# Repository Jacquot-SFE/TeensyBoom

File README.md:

TEENSYBOOM
---
Teensy 3.2 analog emulation drum machine.

# Organization

Supposedly all of the design artifacts will wind up in here.

If it's not here, go check the ol' [synth-drum]() repo.  It's a mess, be warned.

* **/chassis/** files for the cheek blocks & control panel
* **/TeensyBoomVoiceLibrary/** source files for the Teensy-audio-based library
* **/TeensyBoom/** the sketch files for the sequencer and stuff
* **/demo-patterns/** Some pattern files captured after playing with the sequencer a bit.  For use when you get sick of the default pattern.
* **/Documentation/** ha ha.  

## Setup & Configuration

Developed using Arduino IDE 1.6.5.  Last time I tried a newer built, it rebuilt everything everytime I clicked 'go.'

Loading using Teensy Loader 1.28.

### Installation:

Copy the _TeensyVoiceLibrary_ files to your local Arduino library directory (for me , it's C:\Users\redacted\Documents\Arduino\libraries\TeensyBoomVoiceLibrary).

Remove or rename the AudioSynthSimpleDrum in the teensy audio directory (C:\Users\byron.jacquot\Documents\Arduino\libraries\Audio\synth_simple_drum.cpp and .h).  The Boom library contains a newer version.

### Compile and Load:

I've been building for 72 MHz, non-optimized, with the assumption that we can always bump up to optimization & overclocking if we run out of resources.  It's harder to go the other way!

License Information
-------------------

This product is _**open source**_!

Please review the LICENSE.md file for license information.

Distributed as-is; no warranty is given.

It heavily leverages all of the infrastructure developed by [PJRC.com](PJRC.com).  Please support them by purchasing genuine Teensy components!  _Alibaba Teensys aren't Teensies!_

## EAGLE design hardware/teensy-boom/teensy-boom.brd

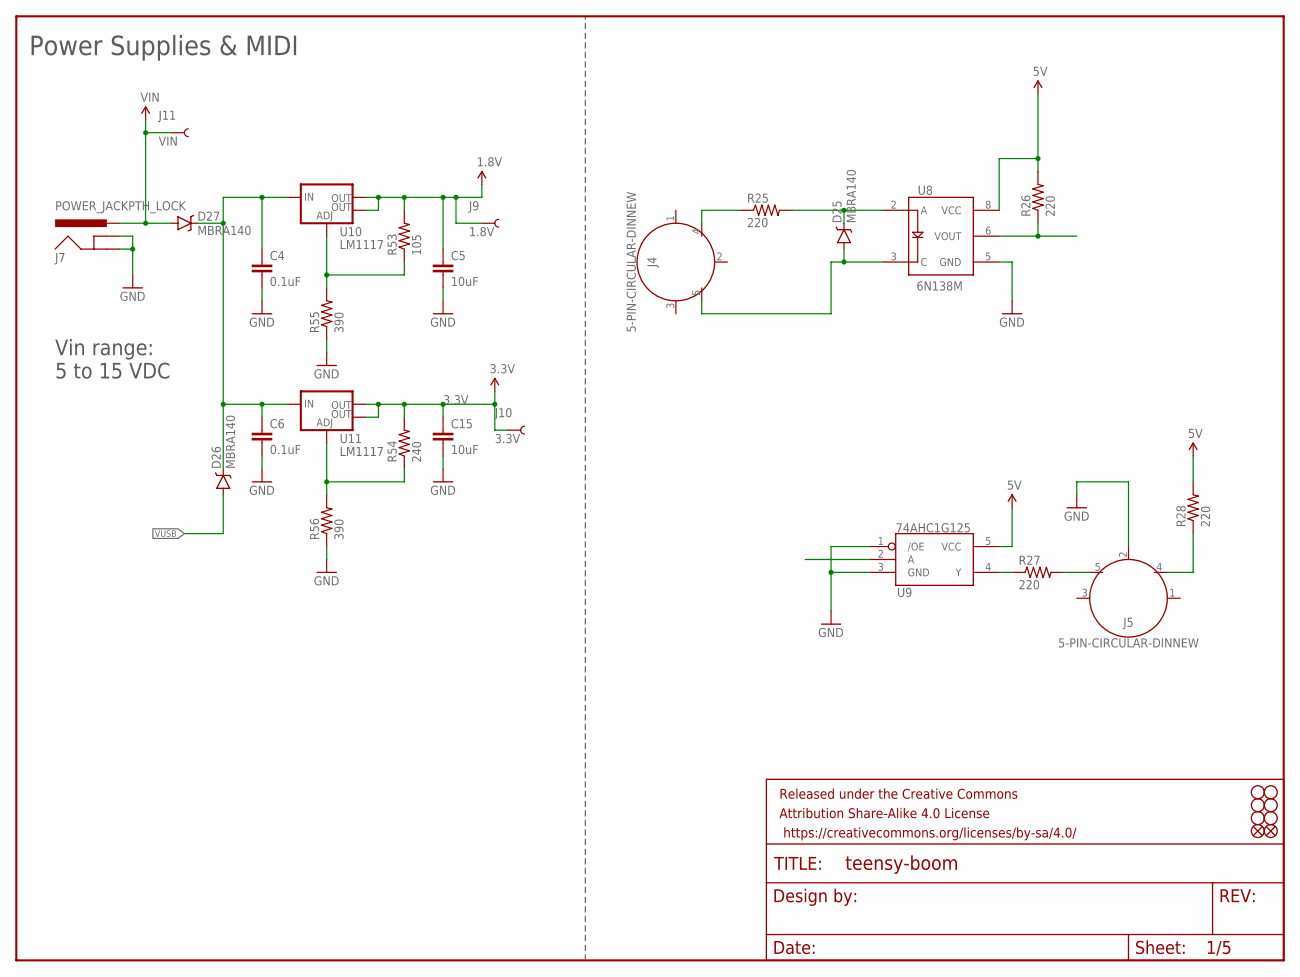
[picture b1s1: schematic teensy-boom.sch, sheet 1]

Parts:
C4, C6: 0.1uF; 0603-CAP
C5, C15: 10uF; 0603-CAP
D25, D26, D27: MBRA140; SMA-DIODE
FD1, FD2: FIDUCIALUFIDUCIAL; MICRO-FIDUCIAL
FRAME2: FRAME-LETTERNO_PACKAGE; DUMMY
H1, H2, H3, H4, H5, H6: STAND-OFF
J4, J5: 5-PIN-CIRCULAR-DINNEW; 5-PIN-DIN-RA-PCB-NEW
J7: POWER_JACKPTH_LOCK; POWER_JACK_PTH_LOCK
J9: 1.8V; TP_15TH
J10: 3.3V; TP_15TH
J11: VIN; TP_15TH
R25, R26, R27, R28: 220; 0603-RES
R53: 105; 0603-RES
R54: 240; 0603-RES
R55, R56: 390; 0603-RES
U8: 6N138M; 8-SMD
U9: 74AHC1G125; SOT23-5
U10, U11: LM1117; SOT223

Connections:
1.8V: C5.1, J9.P$1, R53.2, U10.2 (OUT), U10.4 (OUT); also elsewhere on the board
3.3V: C15.1, J10.P$1, R54.2, U11.2 (OUT), U11.4 (OUT); also elsewhere on the board
5V: R26.2, R28.2, U8.8 (VCC), U9.5 (VCC)
GND: C4.2, C5.2, C6.2, C15.2, J5.2, J7.GND, J7.GNDBREAK, R55.1, R56.1, U8.5 (GND), U9.1 (/OE), U9.3 (GND); also elsewhere on the board
unnamed: J4.4, R25.1
unnamed: D25.C, R25.2, U8.2 (A)
unnamed: D25.A, J4.5, U8.3 (C)
unnamed: R26.1, U8.6 (VOUT)
unnamed: R27.1, U9.4 (Y)
unnamed: J5.5, R27.2
unnamed: J5.4, R28.1
unnamed: C4.1, C6.1, D26.C, D27.C, U10.3 (IN), U11.3 (IN)
unnamed: R53.1, R55.2, U10.1 (ADJ)
unnamed: R54.1, R56.2, U11.1 (ADJ)
VIN: D27.A, J7.PWR, J11.P$1
VUSB: D26.A; also elsewhere on the board

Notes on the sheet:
Power Supplies & MIDI
Vin range: 5 to 15 VDC

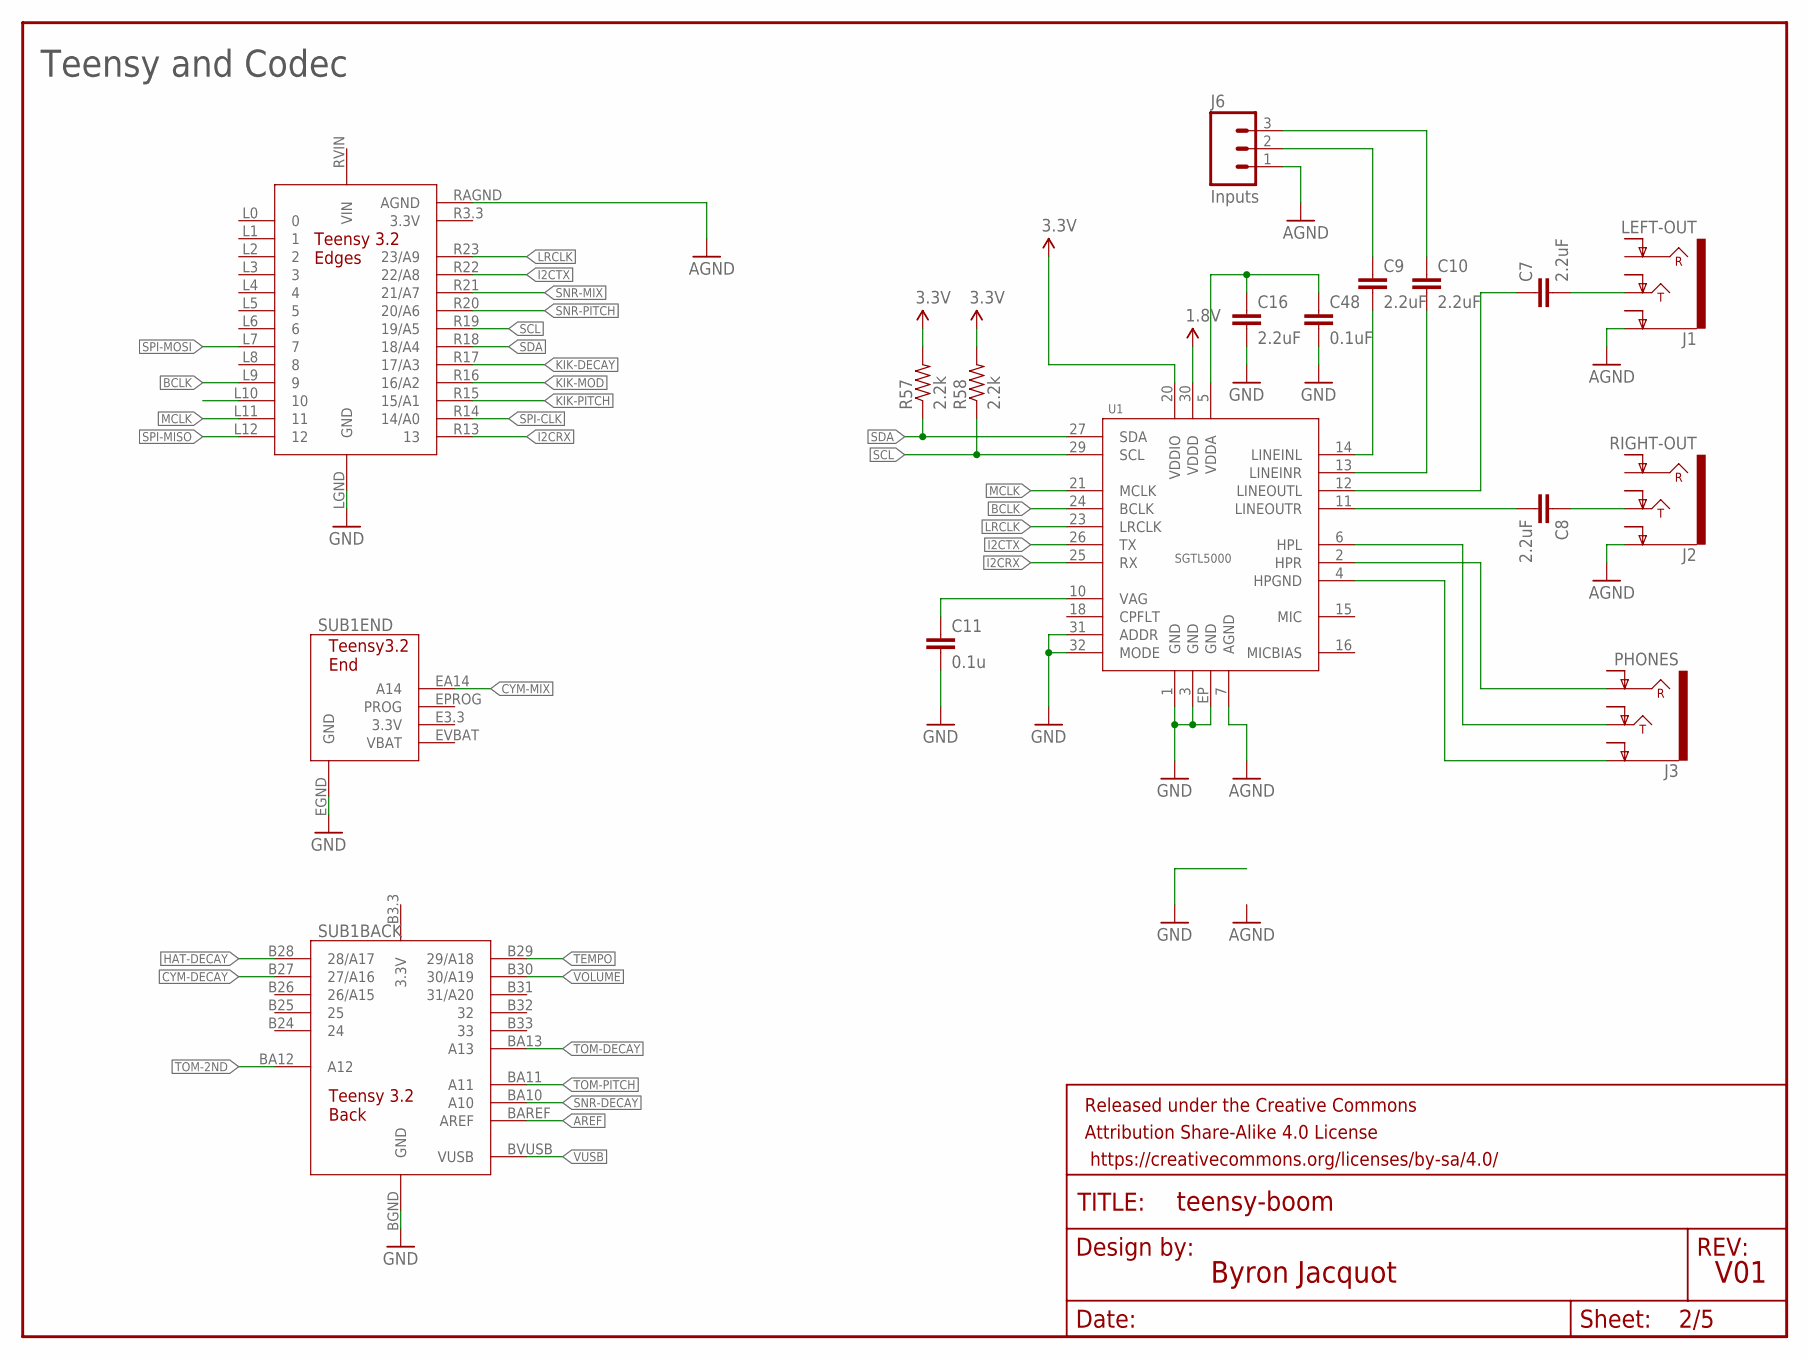
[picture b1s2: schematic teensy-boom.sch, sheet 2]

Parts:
C7, C8, C9, C10, C16: 2.2uF; 0805-CAP
C11: 0.1u; 0805
C48: 0.1uF; 0603-CAP
FRAME1: FRAME-LETTER; CREATIVE_COMMONS
J1: LEFT-OUT; AUDIO-JACK-.25-INCH-HORIZ-PTH
J2: RIGHT-OUT; AUDIO-JACK-.25-INCH-HORIZ-PTH
J3: PHONES; AUDIO-JACK-.25-INCH-HORIZ-PTH
J6: Inputs; 1X03_LOCK
R57, R58: 2.2k; 0603-RES
SUB1: TEENSY-3.2PTH; TEENSY-3.2
U1: SGTL5000; QFN-32

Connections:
1.8V: U1.30 (VDDD); also elsewhere on the board
3.3V: R57.2, R58.2, U1.20 (VDDIO); also elsewhere on the board
AGND: J1.SLEEVE (EARTH), J2.SLEEVE (EARTH), J6.1, SUB1.RAGND (AGND), U1.7 (AGND); also elsewhere on the board
AREF: SUB1.BAREF (AREF); also elsewhere on the board
BCLK: SUB1.L9 (9), U1.24 (BCLK)
CYM-DECAY: SUB1.B27 (27/A16); also elsewhere on the board
CYM-MIX: SUB1.EA14 (A14); also elsewhere on the board
GND: C11.2, C16.2, C48.2, SUB1.BGND (GND), SUB1.EGND (GND), SUB1.LGND (GND), U1.1 (GND), U1.3 (GND), U1.31 (ADDR), U1.32 (MODE), U1.EP (GND); also elsewhere on the board
HAT-DECAY: SUB1.B28 (28/A17); also elsewhere on the board
I2CRX: SUB1.R13 (13), U1.25 (RX)
I2CTX: SUB1.R22 (22/A8), U1.26 (TX)
KIK-DECAY: SUB1.R17 (17/A3); also elsewhere on the board
KIK-MOD: SUB1.R16 (16/A2); also elsewhere on the board
KIK-PITCH: SUB1.R15 (15/A1); also elsewhere on the board
LRCLK: SUB1.R23 (23/A9), U1.23 (LRCLK)
MCLK: SUB1.L11 (11), U1.21 (MCLK)
unnamed: C8.1, J2.TIP
unnamed: C7.2, J1.TIP
unnamed: C8.2, U1.11 (LINEOUTR)
unnamed: C7.1, U1.12 (LINEOUTL)
unnamed: C10.2, U1.13 (LINEINR)
unnamed: C9.2, U1.14 (LINEINL)
unnamed: J3.TIP, U1.6 (HPL)
unnamed: J3.RING, U1.2 (HPR)
unnamed: J3.SLEEVE (EARTH), U1.4 (HPGND)
unnamed: C9.1, J6.2
unnamed: C10.1, J6.3
unnamed: C11.1, U1.10 (VAG)
unnamed: C16.1, C48.1, U1.5 (VDDA)
SCL: R58.1, SUB1.R19 (19/A5), U1.29 (SCL)
SDA: R57.1, SUB1.R18 (18/A4), U1.27 (SDA)
SNR-DECAY: SUB1.BA10 (A10); also elsewhere on the board
SNR-MIX: SUB1.R21 (21/A7); also elsewhere on the board
SNR-PITCH: SUB1.R20 (20/A6); also elsewhere on the board
SPI-CLK: SUB1.R14 (14/A0); also elsewhere on the board
SPI-MISO: SUB1.L12 (12); also elsewhere on the board
SPI-MOSI: SUB1.L7 (7); also elsewhere on the board
TEMPO: SUB1.B29 (29/A18); also elsewhere on the board
TOM-2ND: SUB1.BA12 (A12); also elsewhere on the board
TOM-DECAY: SUB1.BA13 (A13); also elsewhere on the board
TOM-PITCH: SUB1.BA11 (A11); also elsewhere on the board
VOLUME: SUB1.B30 (30/A19); also elsewhere on the board
VUSB: SUB1.BVUSB (VUSB); also elsewhere on the board

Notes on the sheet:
V01
Byron Jacquot
Teensy and Codec

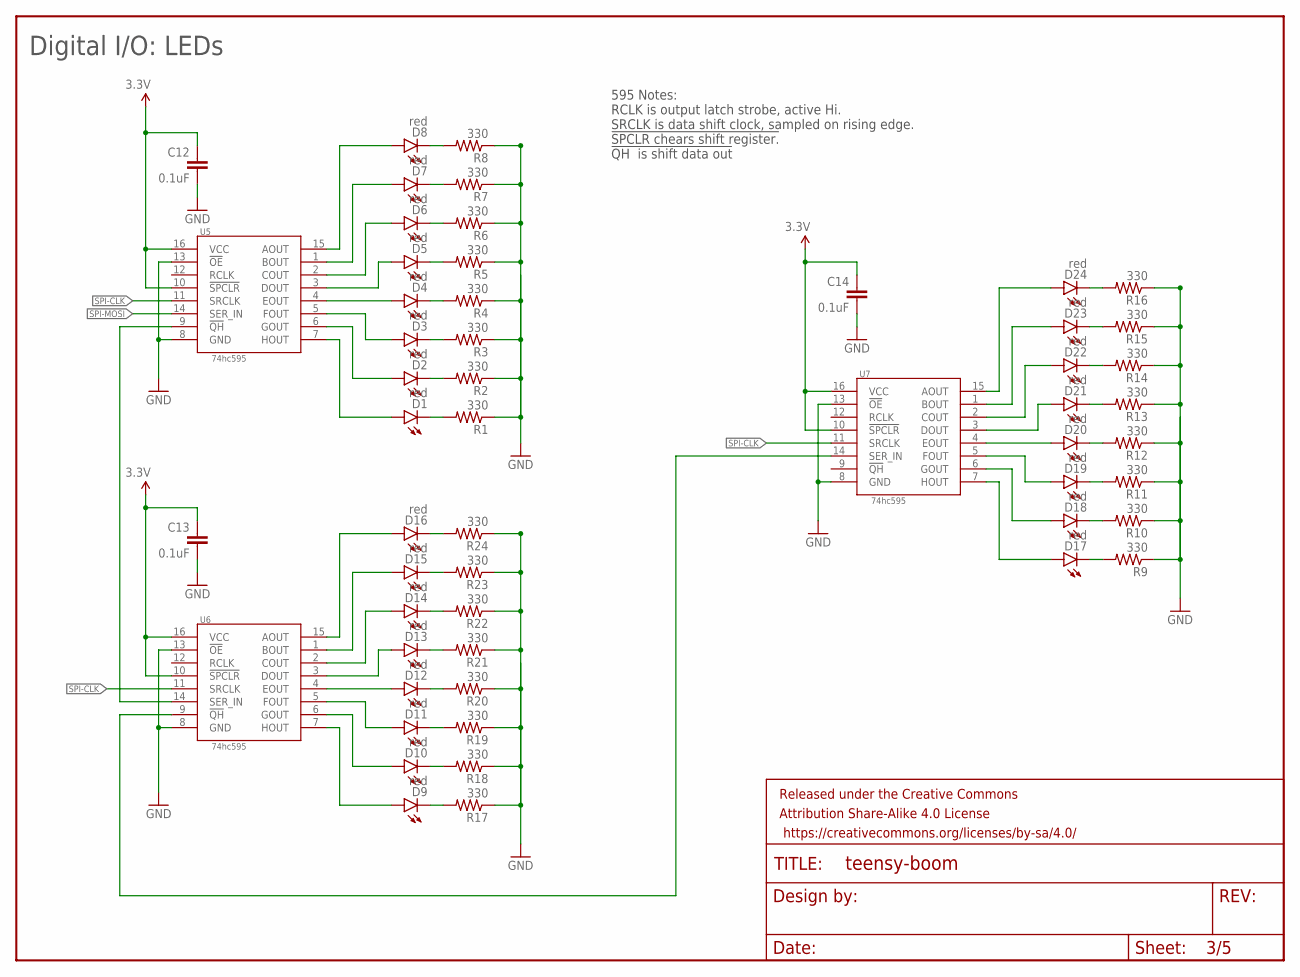
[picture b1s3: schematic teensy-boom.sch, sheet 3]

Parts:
C12, C13, C14: 0.1uF; 0603-CAP
D1, D2, D3, D4, D5, D6, D7, D8, D9, D10, D11, D12, D13, D14, D15, D16, D17, D18, D19, D20, D21, D22, D23, D24: red; LED3MM-NS
FRAME3: FRAME-LETTERNO_PACKAGE; DUMMY
R1, R2, R3, R4, R5, R6, R7, R8, R9, R10, R11, R12, R13, R14, R15, R16, R17, R18, R19, R20, R21, R22, R23, R24: 330; 0603-RES
U5, U6, U7: 74hc595; SO16

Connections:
3.3V: C12.1, C13.1, C14.1, U5.10 (!SPCLR), U5.16 (VCC), U6.10 (!SPCLR), U6.16 (VCC), U7.10 (!SPCLR), U7.16 (VCC); also elsewhere on the board
GND: C12.2, C13.2, C14.2, R1.1, R2.1, R3.1, R4.1, R5.1, R6.1, R7.1, R8.1, R9.1, R10.1, R11.1, R12.1, R13.1, R14.1, R15.1, R16.1, R17.1, R18.1, R19.1, R20.1, R21.1, R22.1, R23.1, R24.1, U5.8 (GND), U5.13 (!OE), U6.8 (GND), U6.13 (!OE), U7.8 (GND), U7.13 (!OE); also elsewhere on the board
unnamed: D1.K (C), R1.2
unnamed: D2.K (C), R2.2
unnamed: D3.K (C), R3.2
unnamed: D4.K (C), R4.2
unnamed: D5.K (C), R5.2
unnamed: D6.K (C), R6.2
unnamed: D7.K (C), R7.2
unnamed: D8.K (C), R8.2
unnamed: D9.K (C), R17.2
unnamed: D10.K (C), R18.2
unnamed: D11.K (C), R19.2
unnamed: D12.K (C), R20.2
unnamed: D13.K (C), R21.2
unnamed: D14.K (C), R22.2
unnamed: D15.K (C), R23.2
unnamed: D16.K (C), R24.2
unnamed: D17.K (C), R9.2
unnamed: D18.K (C), R10.2
unnamed: D19.K (C), R11.2
unnamed: D20.K (C), R12.2
unnamed: D21.K (C), R13.2
unnamed: D22.K (C), R14.2
unnamed: D23.K (C), R15.2
unnamed: D24.K (C), R16.2
unnamed: D5.A, U5.3 (DOUT)
unnamed: D4.A, U5.4 (EOUT)
unnamed: D3.A, U5.5 (FOUT)
unnamed: D2.A, U5.6 (GOUT)
unnamed: D1.A, U5.7 (HOUT)
unnamed: D6.A, U5.2 (COUT)
unnamed: D7.A, U5.1 (BOUT)
unnamed: D8.A, U5.15 (AOUT)
unnamed: D12.A, U6.4 (EOUT)
unnamed: D11.A, U6.5 (FOUT)
unnamed: D10.A, U6.6 (GOUT)
unnamed: D9.A, U6.7 (HOUT)
unnamed: D13.A, U6.3 (DOUT)
unnamed: D14.A, U6.2 (COUT)
unnamed: D15.A, U6.1 (BOUT)
unnamed: D16.A, U6.15 (AOUT)
unnamed: D20.A, U7.4 (EOUT)
unnamed: D19.A, U7.5 (FOUT)
unnamed: D18.A, U7.6 (GOUT)
unnamed: D17.A, U7.7 (HOUT)
unnamed: D21.A, U7.3 (DOUT)
unnamed: D24.A, U7.15 (AOUT)
unnamed: D23.A, U7.1 (BOUT)
unnamed: D22.A, U7.2 (COUT)
unnamed: U5.9 (!QH), U6.14 (SER_IN)
unnamed: U6.9 (!QH), U7.14 (SER_IN)
SPI-CLK: U5.11 (SRCLK); also elsewhere on the board
SPI-MOSI: U5.14 (SER_IN); also elsewhere on the board

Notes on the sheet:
Digital I/O: LEDs
595 Notes: RCLK is output latch strobe, active Hi. SRCLK is data shift clock, sampled on rising edge. !SPCLR chears shift register. !QH is shift data out

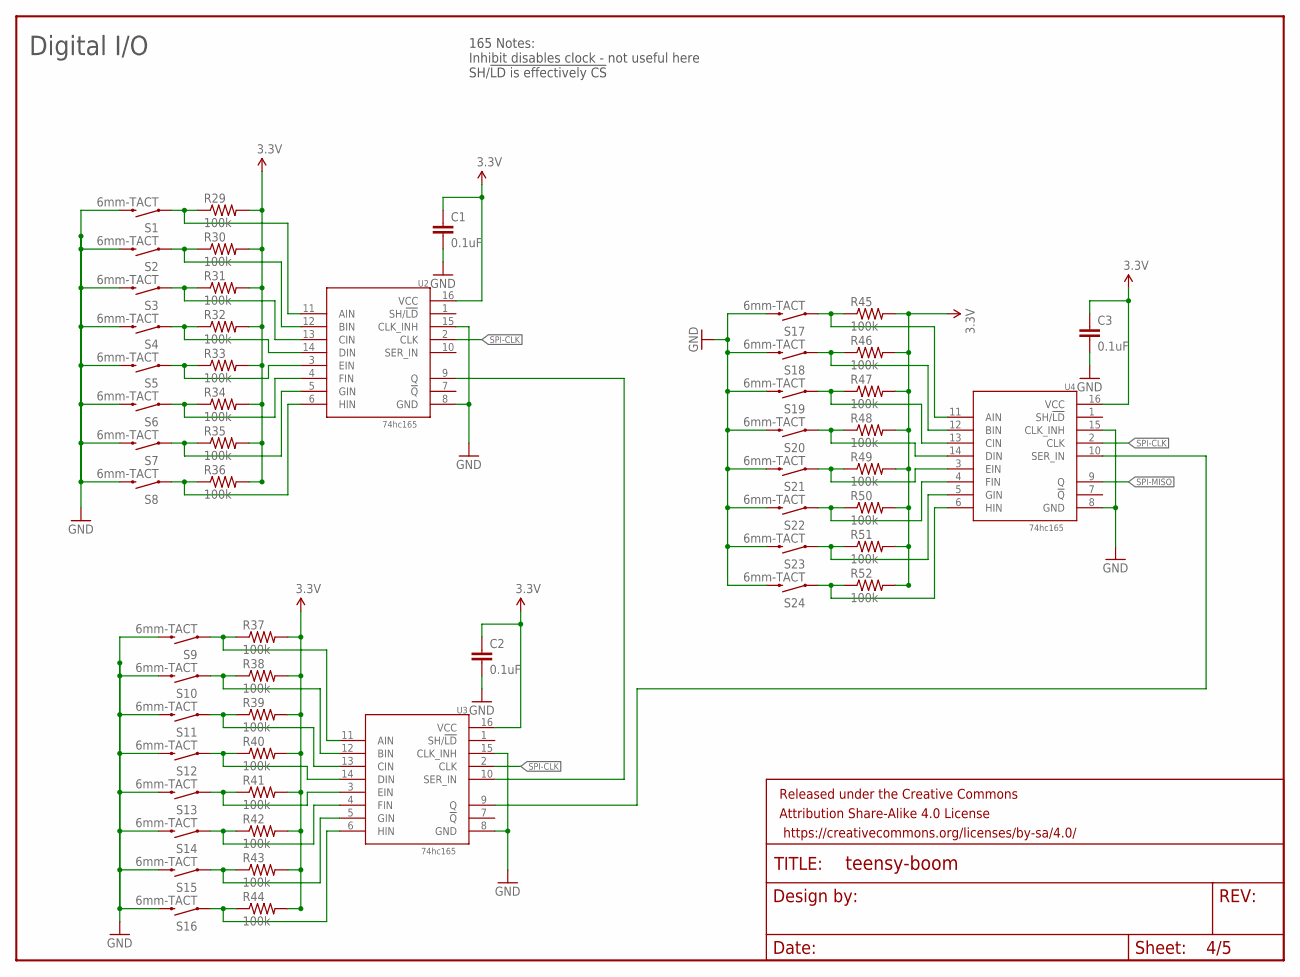
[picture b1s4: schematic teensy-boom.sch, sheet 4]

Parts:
C1, C2, C3: 0.1uF; 0603-CAP
FRAME5: FRAME-LETTERNO_PACKAGE; DUMMY
R29, R30, R31, R32, R33, R34, R35, R36, R37, R38, R39, R40, R41, R42, R43, R44, R45, R46, R47, R48, R49, R50, R51, R52: 100k; 0805
S1, S2, S3, S4, S5, S6, S7, S8, S9, S10, S11, S12, S13, S14, S15, S16, S17, S18, S19, S20, S21, S22, S23, S24: 6mm-TACT; TACTILE-PTH
U2, U3, U4: 74hc165; SO16

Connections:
3.3V: C1.1, C2.1, C3.1, R29.2, R30.2, R31.2, R32.2, R33.2, R34.2, R35.2, R36.2, R37.2, R38.2, R39.2, R40.2, R41.2, R42.2, R43.2, R44.2, R45.2, R46.2, R47.2, R48.2, R49.2, R50.2, R51.2, R52.2, U2.16 (VCC), U3.16 (VCC), U4.16 (VCC); also elsewhere on the board
GND: C1.2, C2.2, C3.2, S1.3 (2), S2.3 (2), S3.3 (2), S4.3 (2), S5.3 (2), S6.3 (2), S7.3 (2), S8.3 (2), S9.3 (2), S10.3 (2), S11.3 (2), S12.3 (2), S13.3 (2), S14.3 (2), S15.3 (2), S16.3 (2), S17.3 (2), S18.3 (2), S19.3 (2), S20.3 (2), S21.3 (2), S22.3 (2), S23.3 (2), S24.3 (2), U2.8 (GND), U2.15 (CLK_INH), U3.8 (GND), U3.15 (CLK_INH), U4.8 (GND), U4.15 (CLK_INH); also elsewhere on the board
unnamed: R35.1, S7.1, U2.5 (GIN)
unnamed: R29.1, S1.1, U2.11 (AIN)
unnamed: R30.1, S2.1, U2.12 (BIN)
unnamed: R31.1, S3.1, U2.13 (CIN)
unnamed: R32.1, S4.1, U2.14 (DIN)
unnamed: R33.1, S5.1, U2.3 (EIN)
unnamed: R34.1, S6.1, U2.4 (FIN)
unnamed: R36.1, S8.1, U2.6 (HIN)
unnamed: R37.1, S9.1, U3.11 (AIN)
unnamed: R38.1, S10.1, U3.12 (BIN)
unnamed: R39.1, S11.1, U3.13 (CIN)
unnamed: R40.1, S12.1, U3.14 (DIN)
unnamed: R41.1, S13.1, U3.3 (EIN)
unnamed: R42.1, S14.1, U3.4 (FIN)
unnamed: R43.1, S15.1, U3.5 (GIN)
unnamed: R44.1, S16.1, U3.6 (HIN)
unnamed: R45.1, S17.1, U4.11 (AIN)
unnamed: R46.1, S18.1, U4.12 (BIN)
unnamed: R47.1, S19.1, U4.13 (CIN)
unnamed: R48.1, S20.1, U4.14 (DIN)
unnamed: R49.1, S21.1, U4.3 (EIN)
unnamed: R50.1, S22.1, U4.4 (FIN)
unnamed: R51.1, S23.1, U4.5 (GIN)
unnamed: U2.9 (Q), U3.10 (SER_IN)
unnamed: U3.9 (Q), U4.10 (SER_IN)
unnamed: R52.1, S24.1, U4.6 (HIN)
SPI-CLK: U2.2 (CLK); also elsewhere on the board
SPI-MISO: U4.9 (Q); also elsewhere on the board

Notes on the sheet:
Digital I/O
165 Notes: Inhibit disables clock - not useful here SH/!LD is effectively CS

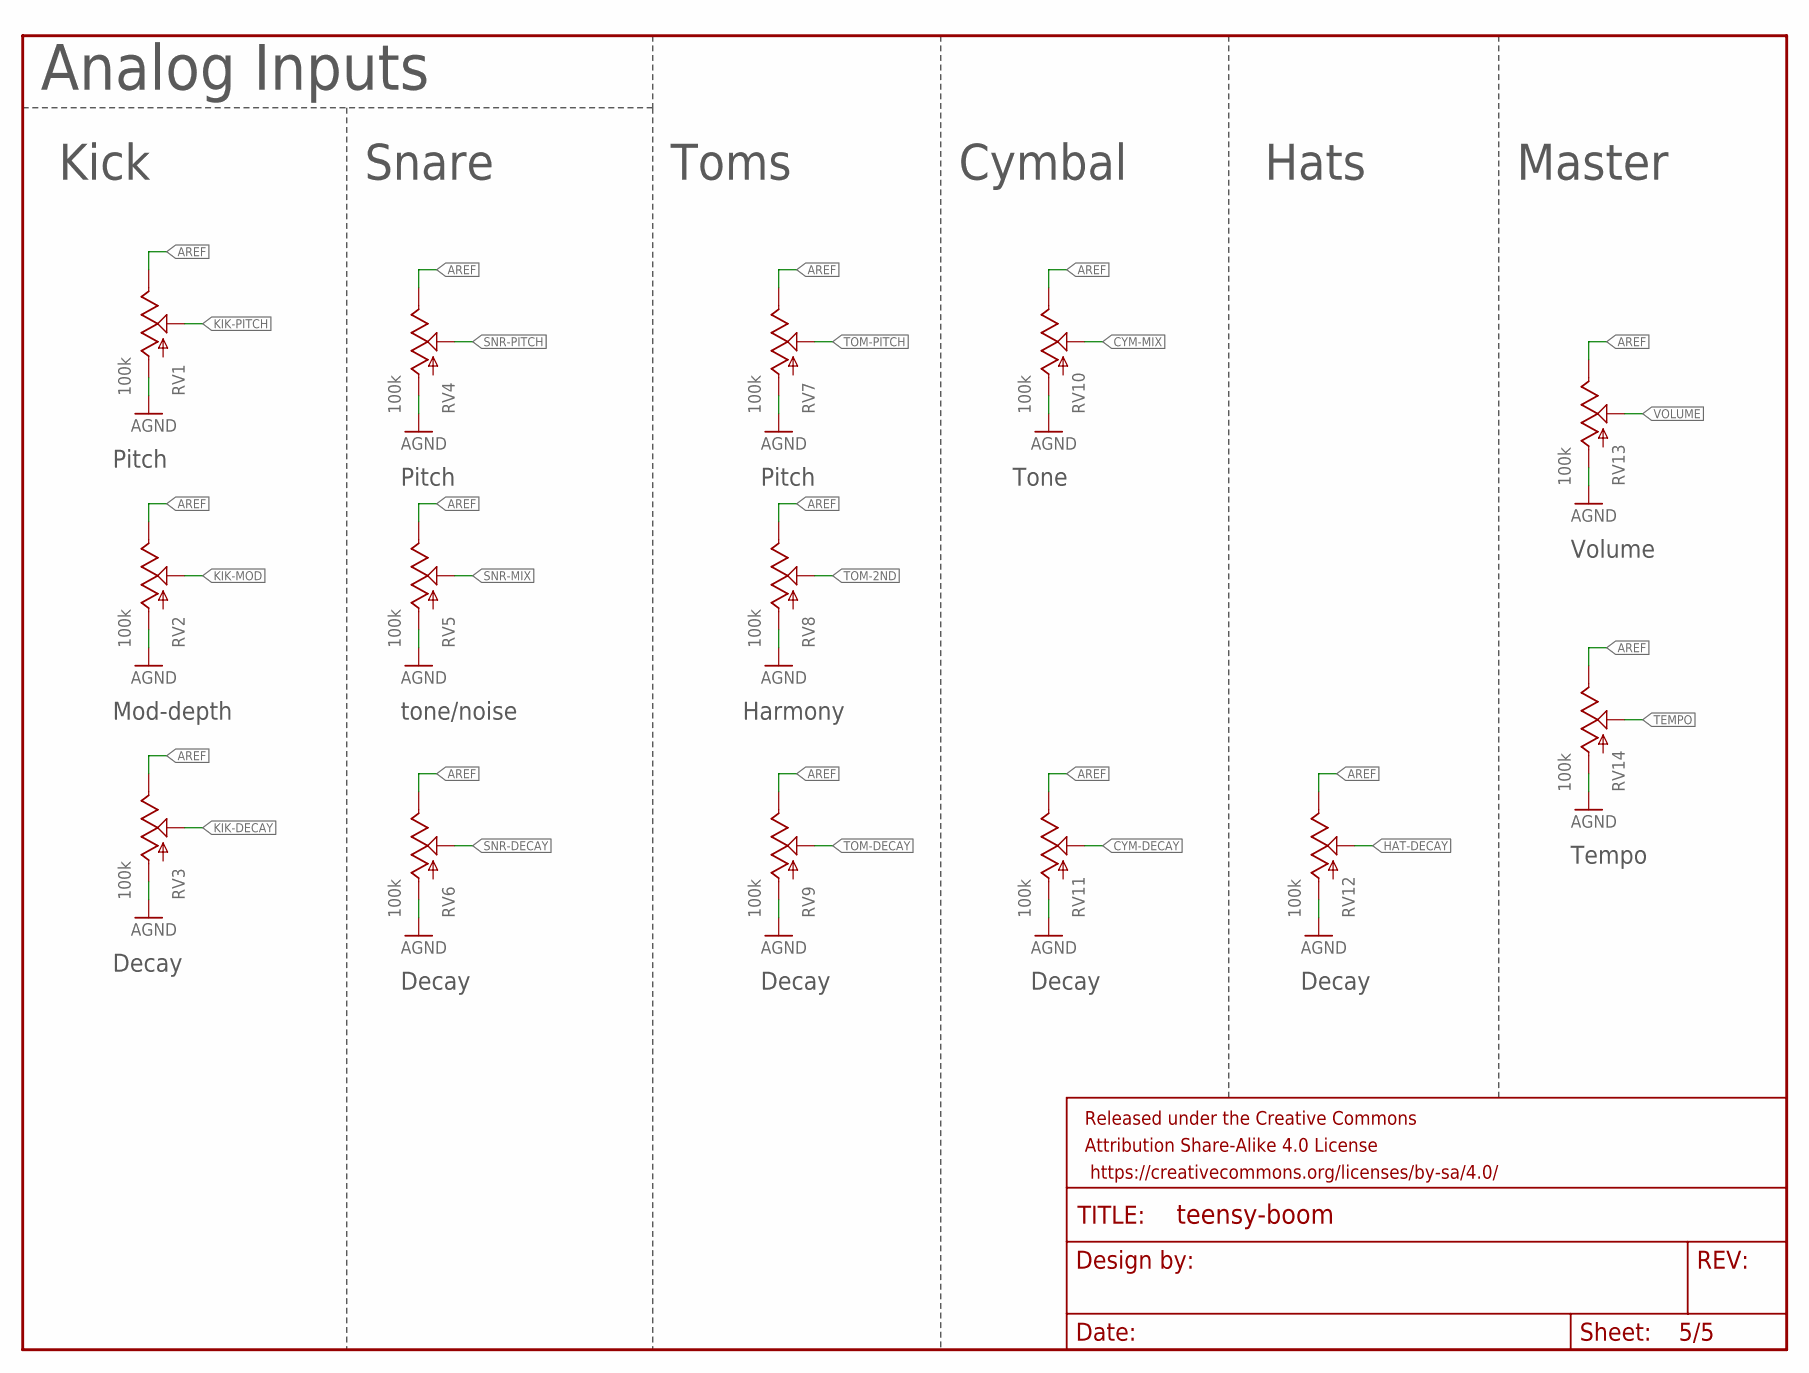
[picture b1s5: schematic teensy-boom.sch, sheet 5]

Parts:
FRAME4: FRAME-LETTERNO_PACKAGE; DUMMY
RV1, RV2, RV3, RV4, RV5, RV6, RV7, RV8, RV9, RV10, RV11, RV12, RV13, RV14: 100k; ALPS_POT_KIT

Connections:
AGND: RV1.P$3 (A), RV2.P$3 (A), RV3.P$3 (A), RV4.P$3 (A), RV5.P$3 (A), RV6.P$3 (A), RV7.P$3 (A), RV8.P$3 (A), RV9.P$3 (A), RV10.P$3 (A), RV11.P$3 (A), RV12.P$3 (A), RV13.P$3 (A), RV14.P$3 (A); also elsewhere on the board
AREF: RV1.P$1 (E), RV2.P$1 (E), RV3.P$1 (E), RV4.P$1 (E), RV5.P$1 (E), RV6.P$1 (E), RV7.P$1 (E), RV8.P$1 (E), RV9.P$1 (E), RV10.P$1 (E), RV11.P$1 (E), RV12.P$1 (E), RV13.P$1 (E), RV14.P$1 (E); also elsewhere on the board
CYM-DECAY: RV11.P$2 (S); also elsewhere on the board
CYM-MIX: RV10.P$2 (S); also elsewhere on the board
HAT-DECAY: RV12.P$2 (S); also elsewhere on the board
KIK-DECAY: RV3.P$2 (S); also elsewhere on the board
KIK-MOD: RV2.P$2 (S); also elsewhere on the board
KIK-PITCH: RV1.P$2 (S); also elsewhere on the board
SNR-DECAY: RV6.P$2 (S); also elsewhere on the board
SNR-MIX: RV5.P$2 (S); also elsewhere on the board
SNR-PITCH: RV4.P$2 (S); also elsewhere on the board
TEMPO: RV14.P$2 (S); also elsewhere on the board
TOM-2ND: RV8.P$2 (S); also elsewhere on the board
TOM-DECAY: RV9.P$2 (S); also elsewhere on the board
TOM-PITCH: RV7.P$2 (S); also elsewhere on the board
VOLUME: RV13.P$2 (S); also elsewhere on the board

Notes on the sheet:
Analog Inputs
Tempo
Volume
Pitch
Mod-depth
Decay
tone/noise
Harmony
Tone
Kick
Snare
Toms
Cymbal
Hats
Master

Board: 2 copper layers, 175 parts (94 on the bottom side), 131 nets, no tracks yet.

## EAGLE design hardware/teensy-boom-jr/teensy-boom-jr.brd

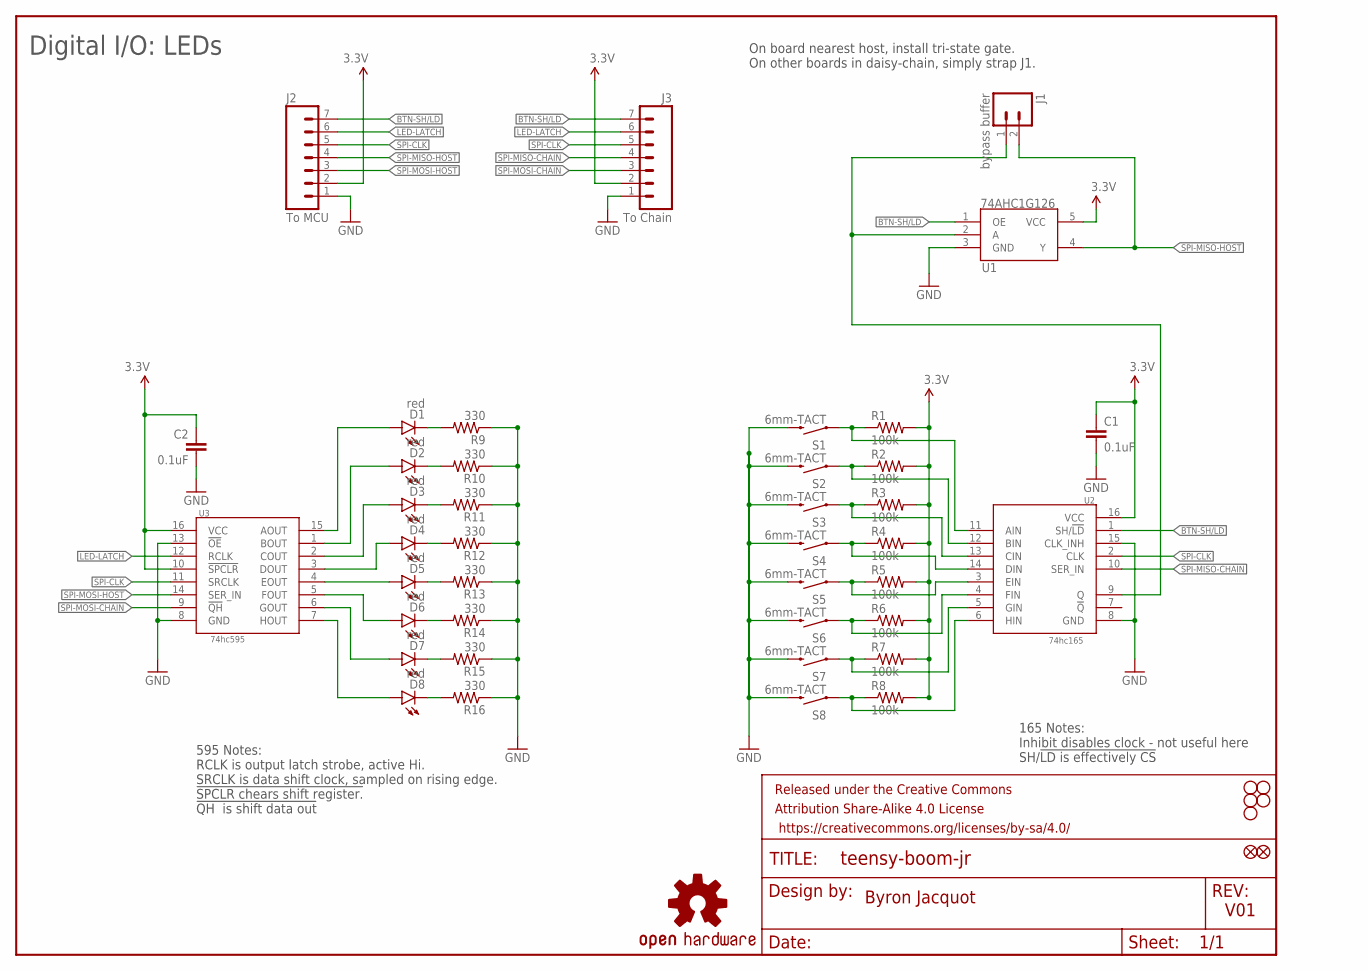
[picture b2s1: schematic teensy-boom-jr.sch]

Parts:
C1, C2: 0.1uF; 0603-CAP
D1, D2, D3, D4, D5, D6, D7, D8: red; LED3MM-NS
FD1, FD2: FIDUCIALUFIDUCIAL; MICRO-FIDUCIAL
FRAME1: FRAME-LETTER; CREATIVE_COMMONS
H1, H2, H3, H4, H5: STAND-OFF
J1: bypass buffer; 1X02_NO_SILK
J2: To MCU; 1X07_NO_SILK
J3: To Chain; 1X07_NO_SILK
LOGO1: OSHW-LOGOS; OSHW-LOGO-S
R1, R2, R3, R4, R5, R6, R7, R8: 100k; 0805
R9, R10, R11, R12, R13, R14, R15, R16: 330; 0603-RES
S1, S2, S3, S4, S5, S6, S7, S8: 6mm-TACT; TACTILE-PTH-12MM
U1: 74AHC1G126; SOT23-5
U2: 74hc165; SO16
U3: 74hc595; SO16

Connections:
3.3V: C1.1, C2.1, J2.2, J3.2, R1.2, R2.2, R3.2, R4.2, R5.2, R6.2, R7.2, R8.2, U1.5 (VCC), U2.16 (VCC), U3.10 (!SPCLR), U3.16 (VCC)
BTN-SH/LD: J2.7, J3.7, U1.1 (OE), U2.1 (SH/!LD)
GND: C1.2, C2.2, J2.1, J3.1, R9.1, R10.1, R11.1, R12.1, R13.1, R14.1, R15.1, R16.1, S1.3 (2), S2.3 (2), S3.3 (2), S4.3 (2), S5.3 (2), S6.3 (2), S7.3 (2), S8.3 (2), U1.3 (GND), U2.8 (GND), U2.15 (CLK_INH), U3.8 (GND), U3.13 (!OE)
LED-LATCH: J2.6, J3.6, U3.12 (RCLK)
unnamed: R1.1, S1.1, U2.11 (AIN)
unnamed: R2.1, S2.1, U2.12 (BIN)
unnamed: R3.1, S3.1, U2.13 (CIN)
unnamed: R4.1, S4.1, U2.14 (DIN)
unnamed: D8.K (C), R16.2
unnamed: R5.1, S5.1, U2.3 (EIN)
unnamed: R6.1, S6.1, U2.4 (FIN)
unnamed: R7.1, S7.1, U2.5 (GIN)
unnamed: D7.K (C), R15.2
unnamed: D6.K (C), R14.2
unnamed: D5.K (C), R13.2
unnamed: D4.K (C), R12.2
unnamed: D3.K (C), R11.2
unnamed: D2.K (C), R10.2
unnamed: D1.K (C), R9.2
unnamed: R8.1, S8.1, U2.6 (HIN)
unnamed: J1.1, U1.2 (A), U2.9 (Q)
unnamed: D4.A, U3.3 (DOUT)
unnamed: D5.A, U3.4 (EOUT)
unnamed: D6.A, U3.5 (FOUT)
unnamed: D7.A, U3.6 (GOUT)
unnamed: D8.A, U3.7 (HOUT)
unnamed: D3.A, U3.2 (COUT)
unnamed: D2.A, U3.1 (BOUT)
unnamed: D1.A, U3.15 (AOUT)
SPI-CLK: J2.5, J3.5, U2.2 (CLK), U3.11 (SRCLK)
SPI-MISO-CHAIN: J3.4, U2.10 (SER_IN)
SPI-MISO-HOST: J1.2, J2.4, U1.4 (Y)
SPI-MOSI-CHAIN: J3.3, U3.9 (!QH)
SPI-MOSI-HOST: J2.3, U3.14 (SER_IN)

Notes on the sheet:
Digital I/O: LEDs
595 Notes: RCLK is output latch strobe, active Hi. SRCLK is data shift clock, sampled on rising edge. !SPCLR chears shift register. !QH is shift data out
On board nearest host, install tri-state gate. On other boards in daisy-chain, simply strap J1.
165 Notes: Inhibit disables clock - not useful here SH/!LD is effectively CS
Byron Jacquot
V01

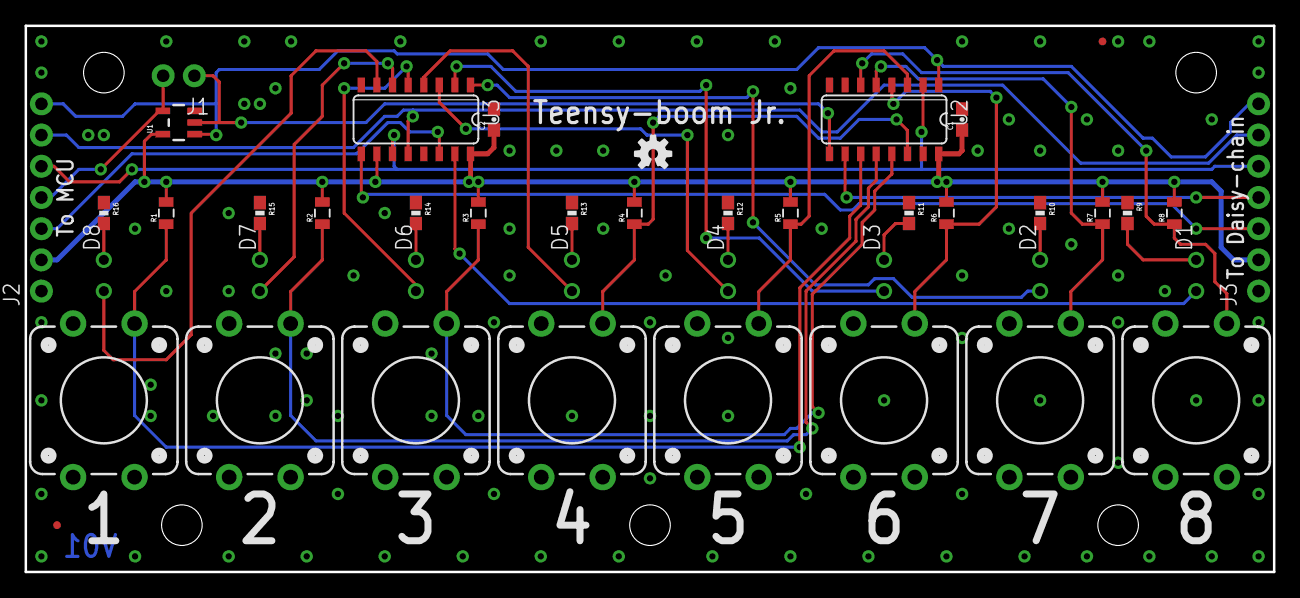
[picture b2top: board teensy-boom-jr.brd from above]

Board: 2 copper layers, 101.6 x 44.5 mm, 49 parts (0 on the bottom side), 34 nets.

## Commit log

2016-06-02 :lollipop: Added .gitattributes & .gitignore files
2016-06-02 First commit - boilerplate
2016-06-03 Initial source file commit.
    It's not building...yet...just a waypoint.
2016-06-03 Maybe it's building now?
    Again, the problem stems from too many copies of the files floating
    around.
2016-06-03 ...or, maybe this one builds...libraries are hard to manage inside repos.
2016-06-16 Adding master volume that touches both line and headphone outs.
2016-06-16 Blinking improvments.
    - Blinks synched to tempo clock...
    - Accents cleared with trigger, so they don't get stranded.
2016-06-17 Incorporating handclap.
2016-06-17 Fixing stuck LEDs in voice selection mode.
2016-06-17 Reworking voice controls.
    Toms now on 4 knobs,
    Cymbal adds 2.
2016-06-22 Adding demo patterns
2016-06-22 Adding Teensy-boom-jr I/O PCB files
2016-06-22 Updating Readme, deleting dead-end "library" directory.
2017-04-12 Adding files that have been sitting here for a long time...

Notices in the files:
parts and their libraries:
SparkFun-Aesthetics: Licensing: Creative Commons ShareAlike 4.0 International - https://creativecommons.org/licenses/by-sa/4.0
SparkFun-Aesthetics: Released under the Creative Commons Attribution Share-Alike 4.0 License
SparkFun-Aesthetics: https://creativecommons.org/licenses/by-sa/4.0
